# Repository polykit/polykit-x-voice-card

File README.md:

# Polykit-X Voice Card

This repository contains schematics and Kicad PCB layout for a voice card with pole-mixing multimode filter. Multiple cards like this are typically used in a polyphonic synthesizer. It can also be used in a monophonic setup. There is only minimal additional circuitry like some pots, input jacks and voltage regulators needed.

Voice card specs:

- Single oscillator with saw, triangle and pulse output
- Multiple VCAs to blend between different input signals, a main VCA for the envelope and a panning VCA for stereo output
- An additional external input that can be mixed in, eg. a noise signal
- One envelope generator for the VCA. It can modulate filter frequency and resonance, also with an inverted signal
- A pole-mixing multimode filter with 8 filter responses:
    - 4P LP
    - 2P LP
    - 4P HP
    - 2P HP
    - 4P BP
    - 2P BP
    - 3P AP + 1P LP
    - 4P N
- There are multiple options two switch and blend between different signals and filter responses
- PWM, FM and synchronization inputs

Video playlist on its functionality and design process: https://www.youtube.com/watch?v=2grRbG7IwDw&list=PLUKLEU8jmlbHH4_13YZM0MI6ez4gYQPfy

## Printed Circuit Boards

Geber files for PCB production [can be downloaded here](plots/).

## Pinout

| Pin # | Description          | Short         | Voltage Range | Type   | Direction | Note |
|-------|----------------------|---------------|---------------|--------|-----------|------|
| 1     | Ground               | GND           |               |        |           |
| 2     | +12V                 | +12V          |               |        |           |
| 3     | -12V                 | -12V          |               |        |           |
| 4     | +5V                  | +5V           |               |        |           |
| 5     | -5V                  | -5V           |               |        |           |
| 6     | Pitch control        | PITCH         | ±5V           | CV     |           | 1
| 7     | PWM                  | PWM           | 0V to 5V      | CV     |           |
| 8     | FM                   | FM            |               | Signal |           |
| 9     | Soft sync            | SSYNC         |               | Signal |           |
| 10    | Hard sync            | HSYNC         |               | Signal |           |
| 11    | Envelope Attack      | ADSR_A        | 0V to -5V     | CV     |           |
| 12    | Envelope Decay       | ADSR_D        | 0V to -5V     | CV     |           |
| 13    | Envelope Sustain     | ADSR_S        | 0V to 5V      | CV     |           |
| 14    | Envelope Release     | ADSR_R        | 0V to -5V     | CV     |           |
| 15    | Envelope Trigger     | TRIG          | 0V/5V         | Trig   |           |
| 16    | Envelope Gate        | GATE          | 0V/5V         | Gate   |           |
| 17    | Envelope Output      | ADSR_OUT      | 0V to 5V      | CV     |           |
| 18    | Enable saw signal    | SAW_ON        | 0V/5V         | Switch |           |
| 19    | Enable triangle sig. | TRIANGLE_ON   | 0V/5V         | Switch |           |
| 20    | Enable ext. signal   | EXTERNAL_ON   | 0V/5V         | Switch |           |
| 21    | Neg. freq. by ADSR   | FREQ_ADSR_NEQ | 0V/5V         | Switch |           |
| 22    | Freq. by ADSR        | FREQ_ADSR     | 0V/5V         | Switch |           |
| 23    | Res. by ADSR         | RES_ADSR      | 0V/5V         | Switch |           |
| 24    | Neg. res. by ADSR    | REF_ADSR_NEQ  | 0V/5V         | Switch |           |
| 25    | Input level 1        | LVL1          | 0V to 5V      | CV     |           |
| 26    | Input level 2        | LVL2          | 0V to 5V      | CV     |           |
| 27    | VCA                  | VCA_CV        | 0V to 5V      | CV     |           |
| 28    | Output panning       | PAN_CV        | -2V to 2V     | CV     |           |
| 29    | External input       | EXTERNAL_IN   |               | Signal |           |
| 30    | Freq. control        | FREQ_CV       | 0V to 5V      | CV     |           |
| 31    | Res. control         | RES_CV        | 0V to 5V      | CV     |           |
| 32    | Filter mode A        | FILTER_MODE_A | 0V/5V         | Switch |           |
| 33    | Filter mode B        | FILTER_MODE_B | 0V/5V         | Switch |           |
| 34    | Filter mode C        | FILTER_MODE_C | 0V/5V         | Switch |           |
| 35    | Output left          | OUT_L         |               | Signal |           | 2
| 36    | Output right         | OUT_R         |               | Signal |           | 2

Note 1: A 100k ohm resistor on pitch CV input is needed. Multiple CV sources can be added by using multiple resistors in parallel

Note 2: Max. output volume can be adjusted by changing R32/R33

## Filter modes

| # | C B A | Filter response |
|---|-------|-----------------|
| 0 | 0 0 0 | 4P LP           |
| 1 | 0 0 1 | 2P LP           |
| 2 | 0 1 0 | 4P HP           |
| 3 | 0 1 1 | 2P HP           |
| 4 | 1 0 0 | 4P BP           |
| 5 | 1 0 1 | 2P BP           |
| 6 | 1 1 0 | 3P AP + 1P LP   |
| 7 | 1 1 1 | 4P N            |

Select filter mode on pins 32-34

0=GND, 1=5V

## Tuning Procedure

### VCO

You need a control voltage 1V/octave source like a keyboard or two fixed, precise voltages in order to tune the VCO. Also a tuning device or a mobile tuning app is needed.

RV3 (TUNE) is for trimming the overall tune, RV5 (SCALE) is for adjusting the distance between two notes.

Take two notes that are one octave apart, eg. C3 and C4. play the first note and trim RV3 to that note.

Now go back and forth between both notes and adjust RV5 so that the correct distance between them gets closer. The first note will drift away while doing this so go back to it by adjusting RV3 again from time to time. Repeat this until both notes are perfectly in tune.

RV4 (HFT) is for trimming the higher frequencies if neccessary.

## BOM

|Reference                                                                                                      |Qnty|Value              |Description                                                                                           |
|---------------------------------------------------------------------------------------------------------|----|-------------------|------------------------------------------------------------------------------------------------------|
|C1, C2, C3, C4, C5, C6, C17, C18, C19, C20, C22, C27, C28, C33, C34, C35, C36, C37, C38, C39, C40       |21  |100n               |Unpolarized capacitor                                                                                 |
|C7, C9, C13, C14, C15, C16                                                                              |6   |2,2uF                |Polarized capacitor                                                                                   |
|C8,                                                                                                      |1   |330p               |Unpolarized capacitor, film or mylar                                                                              |
|C10, C11, C12                                                                                           |3   |33n                |Unpolarized capacitor, film or mylar                                                                                  |
|C21, C23                                                                                                |2   |1n                 |Unpolarized capacitor                                                                                 |
|C24, C25, C29, C30                                                                                      |4   |10n                |Unpolarized capacitor                                                                |
|C26                                                                                                     |1   |1n*                |Unpolarized capacitor, *polypropylene or similar                                                                                 |
|C31                                                                                                     |1   |10n*               |Unpolarized capacitor, *polypropylene or similar                                                                 |
|C32                                                                                                     |1   |33n*               |Unpolarized capacitor, *polypropylene or similar                                                                  |
|D1                                                                                                      |1   |1N4148             |100V 0.15A standard switching diode, DO-35                                                            |
|D2                                                                                                      |1   |LED                |3mm                                                                                  |
|J1                                                                                                      |1   |Conn_01x36         | Pin header 2.54mm 1x36pin 90 degree angle
|Q1                                                                                                      |1   |2N3904             | NPN Transistor, TO-92                                                  |
|R1, R3, R4, R43, R44                                                                                    |5   |1M                 |Resistor                                                                                              |
|R2, R28, R29, R38, R42                                                                                  |4   |470k               |Resistor                                                                                              |
|R5, R6, R7, R21, R22, R24, R25, R54, R55, R56, R60, R63, R68, R73, R74, R75, R76, R93, R101, R102, R103 |21  |10k                |Resistor                                                                                              |
|R8, R9, R10, R11, R12, R13, R14, R15, R18, R19, R20, R69, R70, R71                                      |14  |100k               |Resistor                                                                                              |
|R16, R17, R23                                                                                           |3   |20k                |Resistor                                                                                              |
|R26, R27, R41, R72                                                                                      |4   |68k                |Resistor                                                                                              |
|R30, R31, R34, R35, R37, R64, R65, R66, R67                                                             |9   |1k                 |Resistor                                                                                              |
|R32, R33, R36, R62                                                                                      |4   |33k                |Resistor                                                                                              |
|R39, R40                                                                                                |2   |22k                |Resistor                                                                                              |
|R45                                                                                                     |1   |330k               |Resistor                                                                                              |
|R46                                                                                                     |1   |1M5                |Resistor                                                                                              |
|R47, R48, R57, R58, R59                                                                                 |5   |470                |Resistor                                                                                              |
|R49                                                                                                     |1   |24k                |Resistor                                                                                              |
|R50                                                                                                     |1   |5k6                |Resistor                                                                                              |
|R51                                                                                                     |1   |1k8                |Resistor                                                                                              |
|R52                                                                                                     |1   |10M                |Resistor                                                                                              |
|R53                                                                                                     |1   |47k                |Resistor                                                                                              |
|R61                                                                                                     |1   |680                |Resistor                                                                                              |
|R77, R79, R80, R81, R82, R86, R87, R89, R90, R91, R92, R96                                              |12  |30k                |Resistor                                                                                              |
|R78, R88, R97, R98, R99, R100                                                                           |6   |15k                |Resistor                                                                                              |
|R83, R85, R95                                                                                           |3   |7k5                |Resistor                                                                                              |
|R84, R94                                                                                                |2   |4k99               |Resistor                                                                                              |
|R104                                                                                                    |1   |4k7                |Resistor                                                                                              |
|RV1                                                                                                     |1   |10k NEG_RES_OFFSET |Trim-potentiometer                                                                                    |
|RV2                                                                                                     |1   |10k NEG_FREQ_OFFSET|Trim-potentiometer                                                                                    |
|RV3                                                                                                     |1   |10k TUNE           |Trim-potentiometer                                                                                    |
|RV4                                                                                                     |1   |10k HFT            |Trim-potentiometer                                                                                    |
|RV5                                                                                                     |1   |10k SCALE          |Trim-potentiometer                                                                                    |
|U1, U3                                                                                                  |2   |4016               |Quad Analog Switches                                                                                  |
|U2                                                                                                      |1   |TL072              |Dual Low-Noise JFET-Input Operational Amplifiers, DIP-8/SOIC-8                                        |
|U4, U8, U9                                                                                              |3   |TL074              |Quad Low-Noise JFET-Input Operational Amplifiers, DIP-14/SOIC-14                                      |
|U5                                                                                                      |1   |AS3372E            |4-pole VCF, dual channel input mixer, VCA, panning VCA                                                                                                     |
|U6                                                                                                      |1   |AS3340             |Voltage Controlled Oscillator (VCO), DIP-16/SOIC-16                                                   |
|U7                                                                                                      |1   |AS3310             |ADSR Voltage Controlled Envelope Generator, DIP-16/SOIC-16                                            |
|U10                                                                                                     |1   |CD4051B            |CMOS single 8-channel analog multiplexer demultiplexer, TSSOP-16/DIP-16/SOIC-16                       |

## References

Article on Pole Mixing Filters: https://electricdruid.net/multimode-filters-part-2-pole-mixing-filters

Oberheim Matrix-12 Service Manual: https://archive.org/details/oberheim_MATRIX-12_SERVICE_MANUAL

Oberheim Xpander Service Manual: https://archive.org/details/oberheim_XPANDER_SERVICE_MANUAL

Sequential Prophet T8 Service Manual: https://archive.org/details/sm_SCI_T8_Service_Manual_Complete_sm

AS3372E Datasheet: https://www.ericasynths.lv/media/AS3372E.pdf

AS3310 Datasheet: https://www.alfarzpp.lv/eng/sc/AS3310.pdf

AS3340 Datasheet: https://www.alfarzpp.lv/eng/sc/AS3340.pdf

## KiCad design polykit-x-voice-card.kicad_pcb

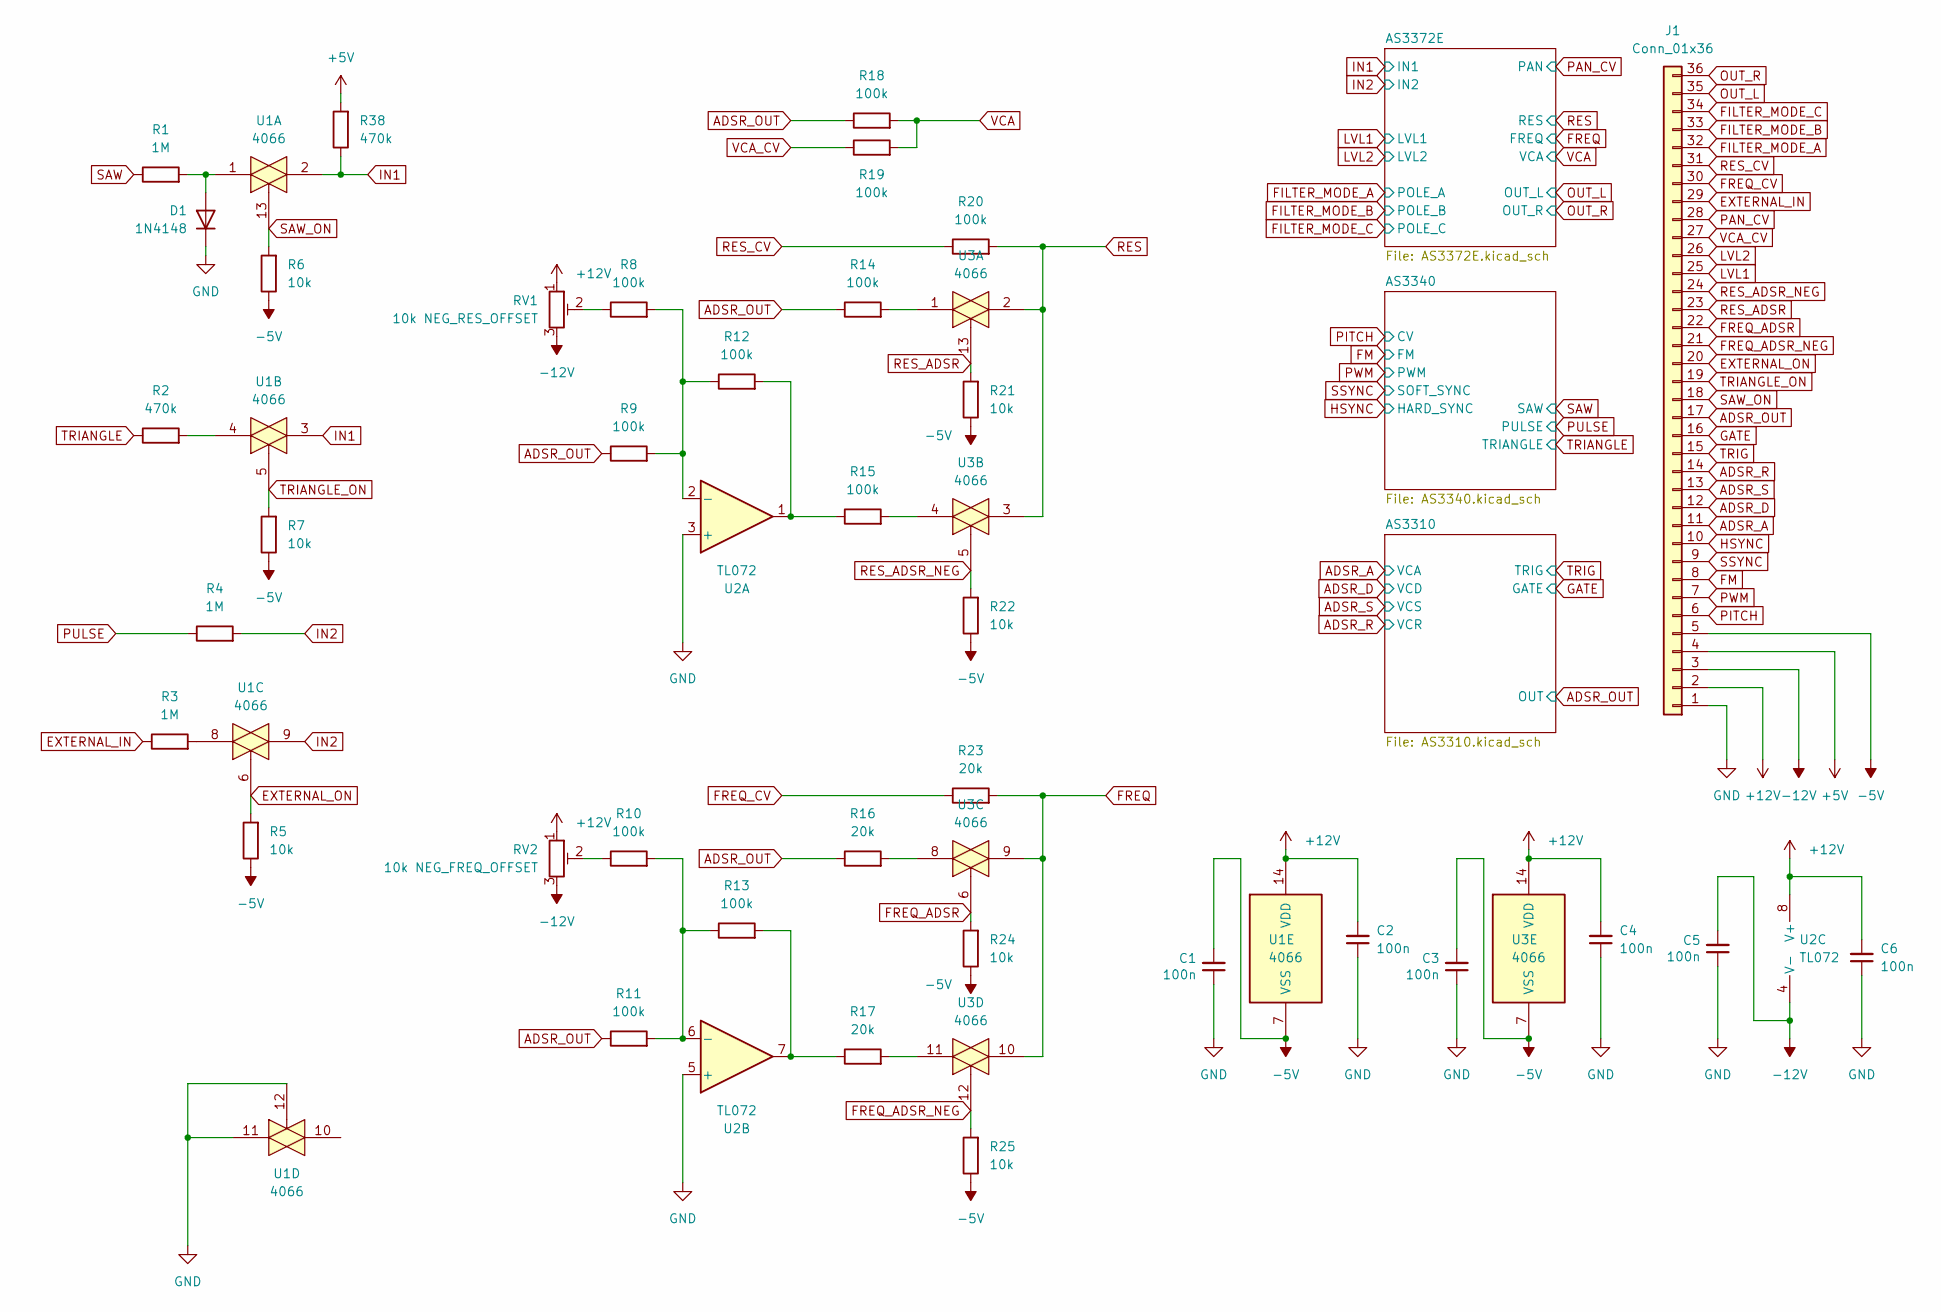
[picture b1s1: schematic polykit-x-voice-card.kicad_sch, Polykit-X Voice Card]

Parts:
C1, C2, C3, C4, C5, C6: 100n; C_Disc_D5.0mm_W2.5mm_P2.50mm
D1: 1N4148; D_DO-35_SOD27_P7.62mm_Horizontal
J1: Conn_01x36; PinHeader_1x36_P2.54mm_Horizontal
R1, R3, R4: 1M; R_Axial_DIN0207_L6.3mm_D2.5mm_P10.16mm_Horizontal
R2, R38: 470k; R_Axial_DIN0207_L6.3mm_D2.5mm_P10.16mm_Horizontal
R5, R6, R7, R21, R22, R24, R25: 10k; R_Axial_DIN0207_L6.3mm_D2.5mm_P10.16mm_Horizontal
R8, R9, R10, R11, R12, R13, R14, R15, R18, R19, R20: 100k; R_Axial_DIN0207_L6.3mm_D2.5mm_P10.16mm_Horizontal
R16, R17, R23: 20k; R_Axial_DIN0207_L6.3mm_D2.5mm_P10.16mm_Horizontal
RV1: 10k NEG_RES_OFFSET; Potentiometer_Bourns_3296W_Vertical
RV2: 10k NEG_FREQ_OFFSET; Potentiometer_Bourns_3296W_Vertical
U1, U3: 4066; DIP-14_W7.62mm_Socket_LongPads
U2: TL072; DIP-8_W7.62mm_Socket_LongPads

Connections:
+5V: J1.4, R38.2; also elsewhere on the board
+12V: C2.2, C4.2, C6.2, J1.2, RV1.1, RV2.1, U1.14 (VDD), U2.8 (V+), U3.14 (VDD); also elsewhere on the board
-5V: C1.2, C3.2, J1.5, R5.1, R6.1, R7.1, R21.1, R22.1, R24.1, R25.1, U1.7 (VSS), U3.7 (VSS); also elsewhere on the board
-12V: C5.2, J1.3, RV1.3, RV2.3, U2.4 (V-); also elsewhere on the board
ADSR_A: J1.11; also elsewhere on the board
ADSR_D: J1.12; also elsewhere on the board
ADSR_OUT: J1.17, R9.1, R11.1, R14.1, R16.1, R18.1; also elsewhere on the board
ADSR_R: J1.14; also elsewhere on the board
ADSR_S: J1.13; also elsewhere on the board
EXTERNAL_IN: J1.29, R3.1
EXTERNAL_ON: J1.20, R5.2, U1.6
FILTER_MODE_A: J1.32; also elsewhere on the board
FILTER_MODE_B: J1.33; also elsewhere on the board
FILTER_MODE_C: J1.34; also elsewhere on the board
FM: J1.8; also elsewhere on the board
FREQ: R23.2, U3.9, U3.10; also elsewhere on the board
FREQ_ADSR: J1.22, R24.2, U3.6
FREQ_ADSR_NEG: J1.21, R25.2, U3.12
FREQ_CV: J1.30, R23.1
GATE: J1.16; also elsewhere on the board
GND: C1.1, C2.1, C3.1, C4.1, C5.1, C6.1, D1.1 (K), J1.1, U1.11, U1.12, U2.3 (+), U2.5 (+); also elsewhere on the board
HSYNC: J1.10; also elsewhere on the board
IN1: R38.1, U1.2, U1.3; also elsewhere on the board
IN2: R4.2, U1.9; also elsewhere on the board
LVL1: J1.25; also elsewhere on the board
LVL2: J1.26; also elsewhere on the board
unnamed: D1.2 (A), R1.2, U1.1
unnamed: R2.2, U1.4
unnamed: R3.2, U1.8
unnamed: R8.1, RV1.2
unnamed: R10.1, RV2.2
unnamed: R10.2, R11.2, R13.1, U2.6 (-)
unnamed: R8.2, R9.2, R12.1, U2.2 (-)
unnamed: R12.2, R15.1, U2.1
unnamed: R13.2, R17.1, U2.7
unnamed: R14.2, U3.1
unnamed: R15.2, U3.4
unnamed: R16.2, U3.8
unnamed: R17.2, U3.11
OUT_L: J1.35; also elsewhere on the board
OUT_R: J1.36; also elsewhere on the board
PAN_CV: J1.28; also elsewhere on the board
PITCH: J1.6; also elsewhere on the board
PULSE: R4.1; also elsewhere on the board
PWM: J1.7; also elsewhere on the board
RES: R20.2, U3.2, U3.3; also elsewhere on the board
RES_ADSR: J1.23, R21.2, U3.13
RES_ADSR_NEG: J1.24, R22.2, U3.5
RES_CV: J1.31, R20.1
SAW: R1.1; also elsewhere on the board
SAW_ON: J1.18, R6.2, U1.13
SSYNC: J1.9; also elsewhere on the board
TRIANGLE: R2.1; also elsewhere on the board
TRIANGLE_ON: J1.19, R7.2, U1.5
TRIG: J1.15; also elsewhere on the board
VCA: R18.2, R19.2; also elsewhere on the board
VCA_CV: J1.27, R19.1

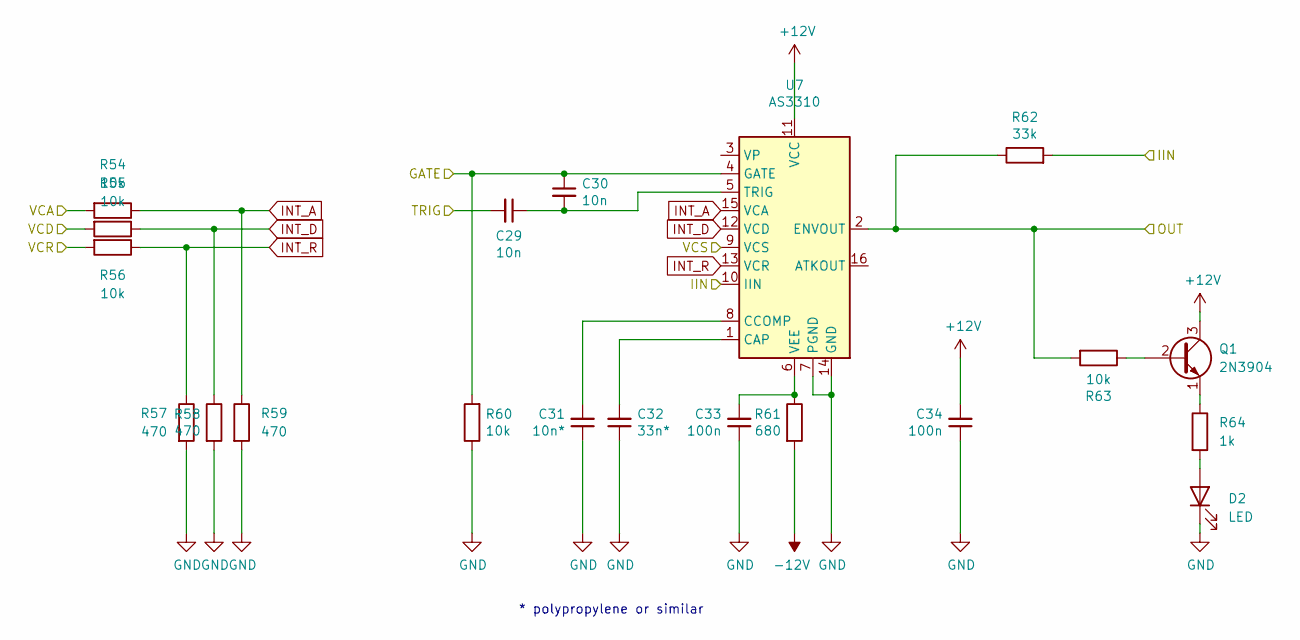
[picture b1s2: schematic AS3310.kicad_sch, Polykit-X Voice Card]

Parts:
C29, C30: 10n; C_Disc_D5.0mm_W2.5mm_P2.50mm
C31: 10n*; C_Rect_L7.2mm_W5.5mm_P5.00mm_FKS2_FKP2_MKS2_MKP2
C32: 33n*; C_Rect_L7.2mm_W5.5mm_P5.00mm_FKS2_FKP2_MKS2_MKP2
C33, C34: 100n; C_Disc_D5.0mm_W2.5mm_P2.50mm
D2: LED; LED_D3.0mm
Q1: 2N3904; TO-92_Inline_Wide
R54, R55, R56, R60, R63: 10k; R_Axial_DIN0207_L6.3mm_D2.5mm_P10.16mm_Horizontal
R57, R58, R59: 470; R_Axial_DIN0207_L6.3mm_D2.5mm_P10.16mm_Horizontal
R61: 680; R_Axial_DIN0207_L6.3mm_D2.5mm_P10.16mm_Horizontal
R62: 33k; R_Axial_DIN0207_L6.3mm_D2.5mm_P10.16mm_Horizontal
R64: 1k; R_Axial_DIN0207_L6.3mm_D2.5mm_P10.16mm_Horizontal
U7: AS3310; DIP-16_W7.62mm_Socket_LongPads

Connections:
+12V: C34.2, Q1.3 (C), U7.11 (VCC); also elsewhere on the board
-12V: R61.2; also elsewhere on the board
/AS3310/IIN: R62.2, U7.10 (IIN)
ADSR_A: R54.2; also elsewhere on the board
ADSR_D: R55.2; also elsewhere on the board
ADSR_OUT: R62.1, R63.2, U7.2 (ENVOUT); also elsewhere on the board
ADSR_R: R56.2; also elsewhere on the board
ADSR_S: U7.9 (VCS); also elsewhere on the board
GATE: C30.1, R60.2, U7.4 (GATE); also elsewhere on the board
GND: C31.1, C32.1, C33.1, C34.1, D2.1 (K), R57.2, R58.2, R59.2, R60.1, U7.7 (PGND), U7.14 (GND); also elsewhere on the board
INT_A: R54.1, R59.1, U7.15 (VCA)
INT_D: R55.1, R58.1, U7.12 (VCD)
INT_R: R56.1, R57.1, U7.13 (VCR)
unnamed: C29.1, C30.2, U7.5 (TRIG)
unnamed: C31.2, U7.8 (CCOMP)
unnamed: C32.2, U7.1 (CAP)
unnamed: C33.2, R61.1, U7.6 (VEE)
unnamed: D2.2 (A), R64.2
unnamed: Q1.1 (E), R64.1
unnamed: Q1.2 (B), R63.1
TRIG: C29.2; also elsewhere on the board

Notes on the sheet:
* polypropylene or similar

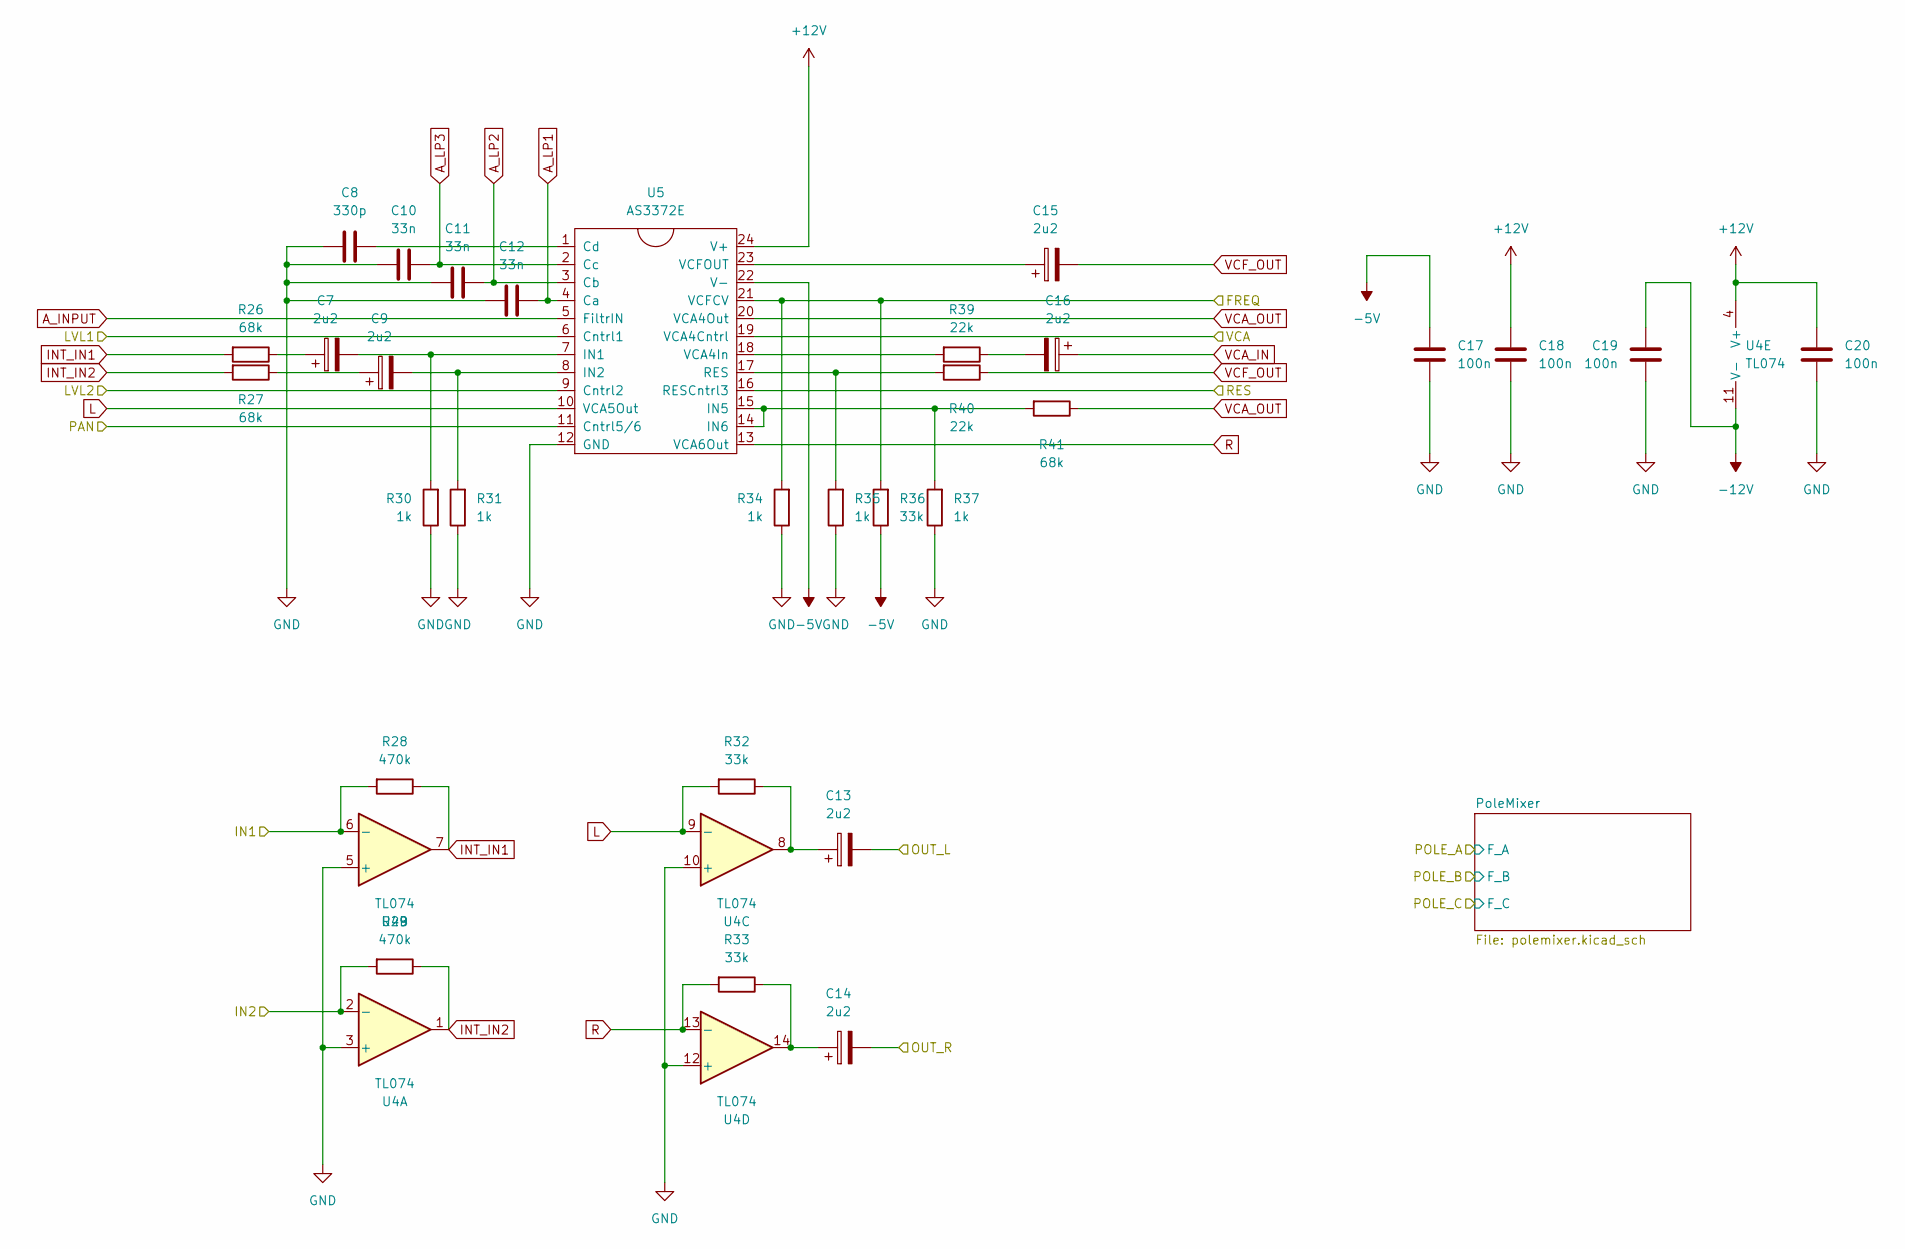
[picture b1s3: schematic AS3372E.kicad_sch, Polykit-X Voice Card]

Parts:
C7, C9, C13, C14, C15, C16: 2u2; CP_Radial_D5.0mm_P2.00mm
C8: 330p; C_Rect_L7.2mm_W3.0mm_P5.00mm_FKS2_FKP2_MKS2_MKP2
C10, C11, C12: 33n; C_Rect_L7.2mm_W3.0mm_P5.00mm_FKS2_FKP2_MKS2_MKP2
C17, C18, C19, C20: 100n; C_Disc_D5.0mm_W2.5mm_P2.50mm
R26, R27, R41: 68k; R_Axial_DIN0207_L6.3mm_D2.5mm_P10.16mm_Horizontal
R28, R29: 470k; R_Axial_DIN0207_L6.3mm_D2.5mm_P10.16mm_Horizontal
R30, R31, R34, R35, R37: 1k; R_Axial_DIN0207_L6.3mm_D2.5mm_P10.16mm_Horizontal
R32, R33, R36: 33k; R_Axial_DIN0207_L6.3mm_D2.5mm_P10.16mm_Horizontal
R39, R40: 22k; R_Axial_DIN0207_L6.3mm_D2.5mm_P10.16mm_Horizontal
U4: TL074; DIP-14_W7.62mm_Socket_LongPads
U5: AS3372E; DIP-24_W7.62mm_Socket_LongPads

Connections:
+12V: C18.1, C20.2, U4.4 (V+), U5.24 (V+); also elsewhere on the board
-5V: C17.1, R36.1, U5.22 (V-); also elsewhere on the board
-12V: C19.2, U4.11 (V-); also elsewhere on the board
A_INPUT: U5.5 (FiltrIN); also elsewhere on the board
A_LP1: C12.2, U5.4 (Ca); also elsewhere on the board
A_LP2: C11.2, U5.3 (Cb); also elsewhere on the board
A_LP3: C10.2, U5.2 (Cc); also elsewhere on the board
FREQ: R34.2, R36.2, U5.21 (VCFCV); also elsewhere on the board
GND: C8.1, C10.1, C11.1, C12.1, C17.2, C18.2, C19.1, C20.1, R30.1, R31.1, R34.1, R35.1, R37.1, U4.3 (+), U4.5 (+), U4.10 (+), U4.12 (+), U5.12 (GND); also elsewhere on the board
IN1: R28.2, U4.6 (-); also elsewhere on the board
IN2: R29.2, U4.2 (-); also elsewhere on the board
INT_IN1: R26.2, R28.1, U4.7
INT_IN2: R27.2, R29.1, U4.1
L: R32.2, U4.9 (-), U5.10 (VCA5Out)
LVL1: U5.6 (Cntrl1); also elsewhere on the board
LVL2: U5.9 (Cntrl2); also elsewhere on the board
unnamed: C7.1, R26.1
unnamed: C7.2, R30.2, U5.7 (IN1)
unnamed: C8.2, U5.1 (Cd)
unnamed: C9.1, R27.1
unnamed: C9.2, R31.2, U5.8 (IN2)
unnamed: C13.1, R32.1, U4.8
unnamed: C14.1, R33.1, U4.14
unnamed: C15.1, U5.23 (VCFOUT)
unnamed: C16.2, R39.1
unnamed: R35.2, R40.2, U5.17 (RES)
unnamed: R37.2, R41.2, U5.14 (IN6), U5.15 (IN5)
unnamed: R39.2, U5.18 (VCA4In)
OUT_L: C13.2; also elsewhere on the board
OUT_R: C14.2; also elsewhere on the board
PAN_CV: U5.11 (Cntrl5/6); also elsewhere on the board
R: R33.2, U4.13 (-), U5.13 (VCA6Out)
RES: U5.16 (RESCntrl3); also elsewhere on the board
VCA: U5.19 (VCA4Cntrl); also elsewhere on the board
VCA_IN: C16.1; also elsewhere on the board
VCA_OUT: R41.1, U5.20 (VCA4Out)
VCF_OUT: C15.2, R40.1; also elsewhere on the board

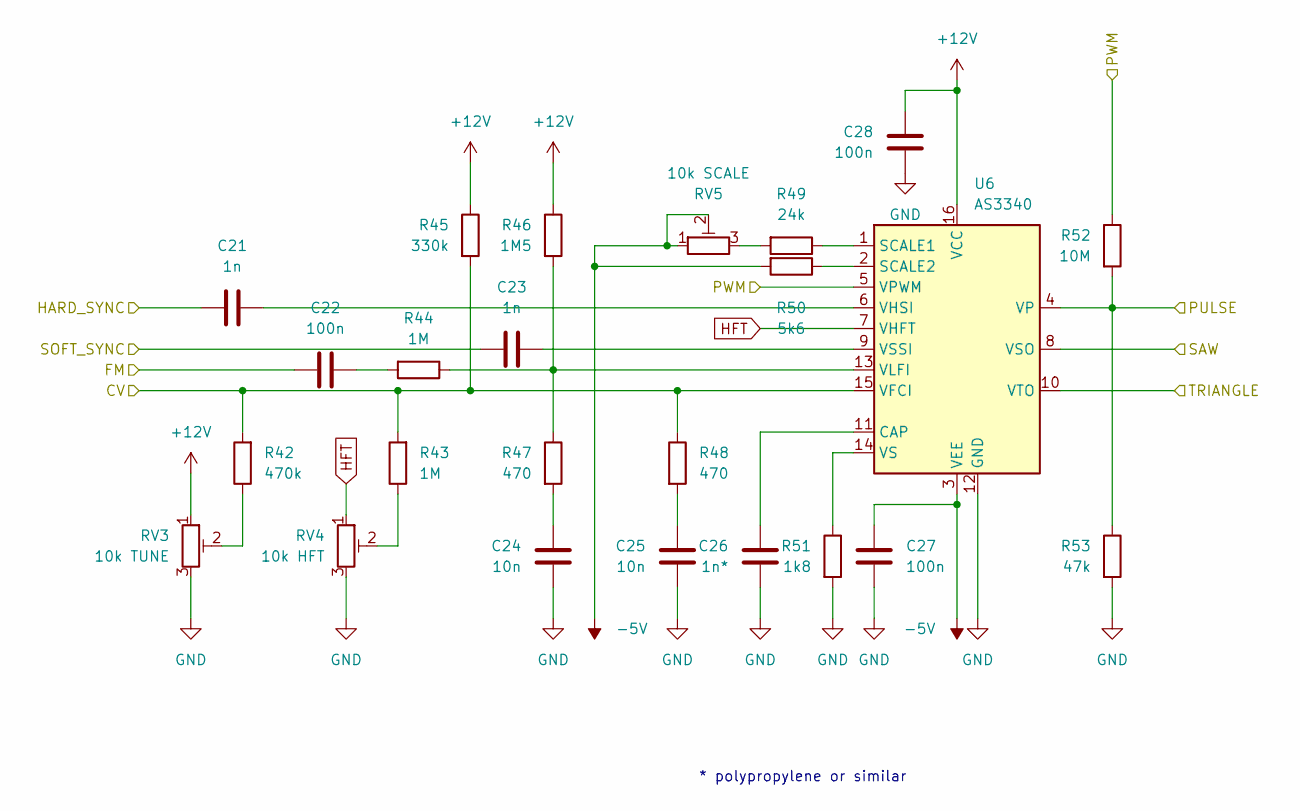
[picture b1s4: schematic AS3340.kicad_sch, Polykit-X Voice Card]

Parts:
C21, C23: 1n; C_Disc_D5.0mm_W2.5mm_P2.50mm
C22, C27, C28: 100n; C_Disc_D5.0mm_W2.5mm_P2.50mm
C24, C25: 10n; C_Disc_D5.0mm_W2.5mm_P2.50mm
C26: 1n*; C_Rect_L7.2mm_W4.5mm_P5.00mm_FKS2_FKP2_MKS2_MKP2
R42: 470k; R_Axial_DIN0207_L6.3mm_D2.5mm_P10.16mm_Horizontal
R43, R44: 1M; R_Axial_DIN0207_L6.3mm_D2.5mm_P10.16mm_Horizontal
R45: 330k; R_Axial_DIN0207_L6.3mm_D2.5mm_P10.16mm_Horizontal
R46: 1M5; R_Axial_DIN0207_L6.3mm_D2.5mm_P10.16mm_Horizontal
R47, R48: 470; R_Axial_DIN0207_L6.3mm_D2.5mm_P10.16mm_Horizontal
R49: 24k; R_Axial_DIN0207_L6.3mm_D2.5mm_P10.16mm_Horizontal
R50: 5k6; R_Axial_DIN0207_L6.3mm_D2.5mm_P10.16mm_Horizontal
R51: 1k8; R_Axial_DIN0207_L6.3mm_D2.5mm_P10.16mm_Horizontal
R52: 10M; R_Axial_DIN0207_L6.3mm_D2.5mm_P10.16mm_Horizontal
R53: 47k; R_Axial_DIN0207_L6.3mm_D2.5mm_P10.16mm_Horizontal
RV3: 10k TUNE; Potentiometer_Bourns_3296W_Vertical
RV4: 10k HFT; Potentiometer_Bourns_3296W_Vertical
RV5: 10k SCALE; Potentiometer_Bourns_3296W_Vertical
U6: AS3340; DIP-16_W7.62mm_Socket_LongPads

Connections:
+12V: C28.1, R45.1, R46.1, RV3.1, U6.16 (VCC); also elsewhere on the board
-5V: C27.1, R50.2, RV5.1, RV5.2, U6.3 (VEE); also elsewhere on the board
FM: C22.2; also elsewhere on the board
GND: C24.2, C25.2, C26.2, C27.2, C28.2, R51.2, R53.2, RV3.3, RV4.3, U6.12 (GND); also elsewhere on the board
HFT: RV4.1, U6.7 (VHFT)
HSYNC: C21.1; also elsewhere on the board
unnamed: C21.2, U6.6 (VHSI)
unnamed: C22.1, R44.2
unnamed: C23.2, U6.9 (VSSI)
unnamed: C24.1, R47.2
unnamed: C25.1, R48.2
unnamed: C26.1, U6.11 (CAP)
unnamed: R42.1, RV3.2
unnamed: R43.1, RV4.2
unnamed: R44.1, R46.2, R47.1, U6.13 (VLFI)
unnamed: R49.1, U6.1 (SCALE1)
unnamed: R49.2, RV5.3
unnamed: R50.1, U6.2 (SCALE2)
unnamed: R51.1, U6.14 (VS)
PITCH: R42.2, R43.2, R45.2, R48.1, U6.15 (VFCI); also elsewhere on the board
PULSE: R52.2, R53.1, U6.4 (VP); also elsewhere on the board
PWM: R52.1, U6.5 (VPWM); also elsewhere on the board
SAW: U6.8 (VSO); also elsewhere on the board
SSYNC: C23.1; also elsewhere on the board
TRIANGLE: U6.10 (VTO); also elsewhere on the board

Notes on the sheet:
* polypropylene or similar

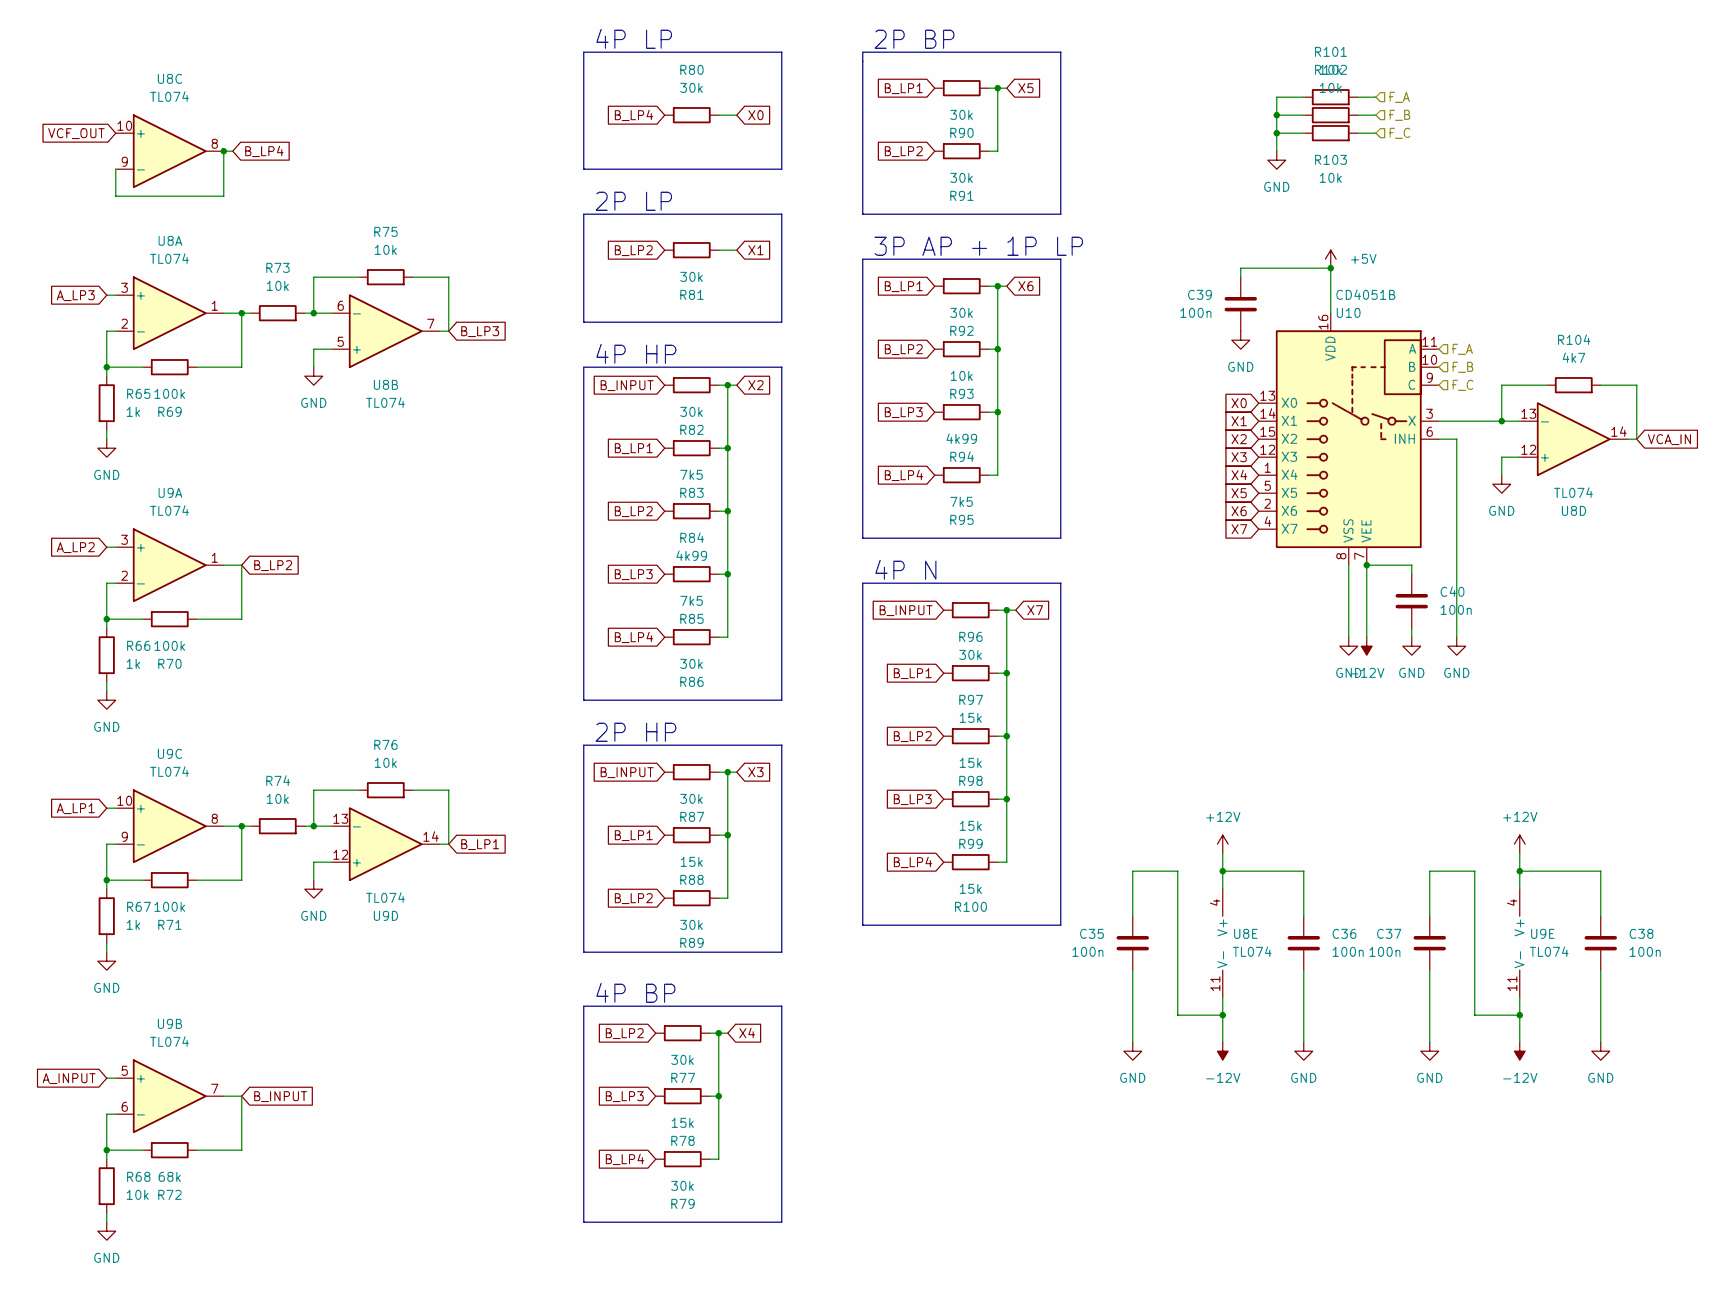
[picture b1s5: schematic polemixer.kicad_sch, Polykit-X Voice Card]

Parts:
C35, C36, C37, C38, C39, C40: 100n; C_Disc_D5.0mm_W2.5mm_P2.50mm
R65, R66, R67: 1k; R_Axial_DIN0207_L6.3mm_D2.5mm_P10.16mm_Horizontal
R68, R73, R74, R75, R76, R93, R101, R102, R103: 10k; R_Axial_DIN0207_L6.3mm_D2.5mm_P10.16mm_Horizontal
R69, R70, R71: 100k; R_Axial_DIN0207_L6.3mm_D2.5mm_P10.16mm_Horizontal
R72: 68k; R_Axial_DIN0207_L6.3mm_D2.5mm_P10.16mm_Horizontal
R77, R79, R80, R81, R82, R86, R87, R89, R90, R91, R92, R96: 30k; R_Axial_DIN0207_L6.3mm_D2.5mm_P10.16mm_Horizontal
R78, R88, R97, R98, R99, R100: 15k; R_Axial_DIN0207_L6.3mm_D2.5mm_P10.16mm_Horizontal
R83, R85, R95: 7k5; R_Axial_DIN0207_L6.3mm_D2.5mm_P10.16mm_Horizontal
R84, R94: 4k99; R_Axial_DIN0207_L6.3mm_D2.5mm_P10.16mm_Horizontal
R104: 4k7; R_Axial_DIN0207_L6.3mm_D2.5mm_P10.16mm_Horizontal
U8, U9: TL074; DIP-14_W7.62mm_Socket_LongPads
U10: CD4051B; DIP-16_W7.62mm_Socket_LongPads

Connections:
+5V: C39.2, U10.16 (VDD); also elsewhere on the board
+12V: C36.2, C38.2, U8.4 (V+), U9.4 (V+); also elsewhere on the board
-12V: C35.2, C37.2, C40.2, U8.11 (V-), U9.11 (V-), U10.7 (VEE); also elsewhere on the board
A_INPUT: U9.5 (+); also elsewhere on the board
A_LP1: U9.10 (+); also elsewhere on the board
A_LP2: U9.3 (+); also elsewhere on the board
A_LP3: U8.3 (+); also elsewhere on the board
B_INPUT: R72.1, R82.2, R87.2, R96.2, U9.7
B_LP1: R76.2, R83.2, R88.2, R90.2, R92.2, R97.2, U9.14
B_LP2: R70.1, R77.2, R81.2, R84.2, R89.2, R91.2, R93.2, R98.2, U9.1
B_LP3: R75.2, R78.2, R85.2, R94.2, R99.2, U8.7
B_LP4: R79.2, R80.2, R86.2, R95.2, R100.2, U8.8, U8.9 (-)
FILTER_MODE_A: R101.2, U10.11 (A); also elsewhere on the board
FILTER_MODE_B: R102.2, U10.10 (B); also elsewhere on the board
FILTER_MODE_C: R103.2, U10.9 (C); also elsewhere on the board
GND: C35.1, C36.1, C37.1, C38.1, C39.1, C40.1, R65.2, R66.2, R67.2, R68.2, R101.1, R102.1, R103.1, U8.5 (+), U8.12 (+), U9.12 (+), U10.6 (INH), U10.8 (VSS); also elsewhere on the board
unnamed: R65.1, R69.2, U8.2 (-)
unnamed: R66.1, R70.2, U9.2 (-)
unnamed: R67.1, R71.2, U9.9 (-)
unnamed: R68.1, R72.2, U9.6 (-)
unnamed: R69.1, R73.1, U8.1
unnamed: R71.1, R74.1, U9.8
unnamed: R73.2, R75.1, U8.6 (-)
unnamed: R74.2, R76.1, U9.13 (-)
unnamed: R104.1, U8.13 (-), U10.3 (X)
VCA_IN: R104.2, U8.14; also elsewhere on the board
VCF_OUT: U8.10 (+); also elsewhere on the board
X0: R80.1, U10.13 (X0)
X1: R81.1, U10.14 (X1)
X2: R82.1, R83.1, R84.1, R85.1, R86.1, U10.15 (X2)
X3: R87.1, R88.1, R89.1, U10.12 (X3)
X4: R77.1, R78.1, R79.1, U10.1 (X4)
X5: R90.1, R91.1, U10.5 (X5)
X6: R92.1, R93.1, R94.1, R95.1, U10.2 (X6)
X7: R96.1, R97.1, R98.1, R99.1, R100.1, U10.4 (X7)

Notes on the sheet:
2P LP
2P HP
3P AP + 1P LP
4P LP
4P BP
2P BP
4P HP
4P N

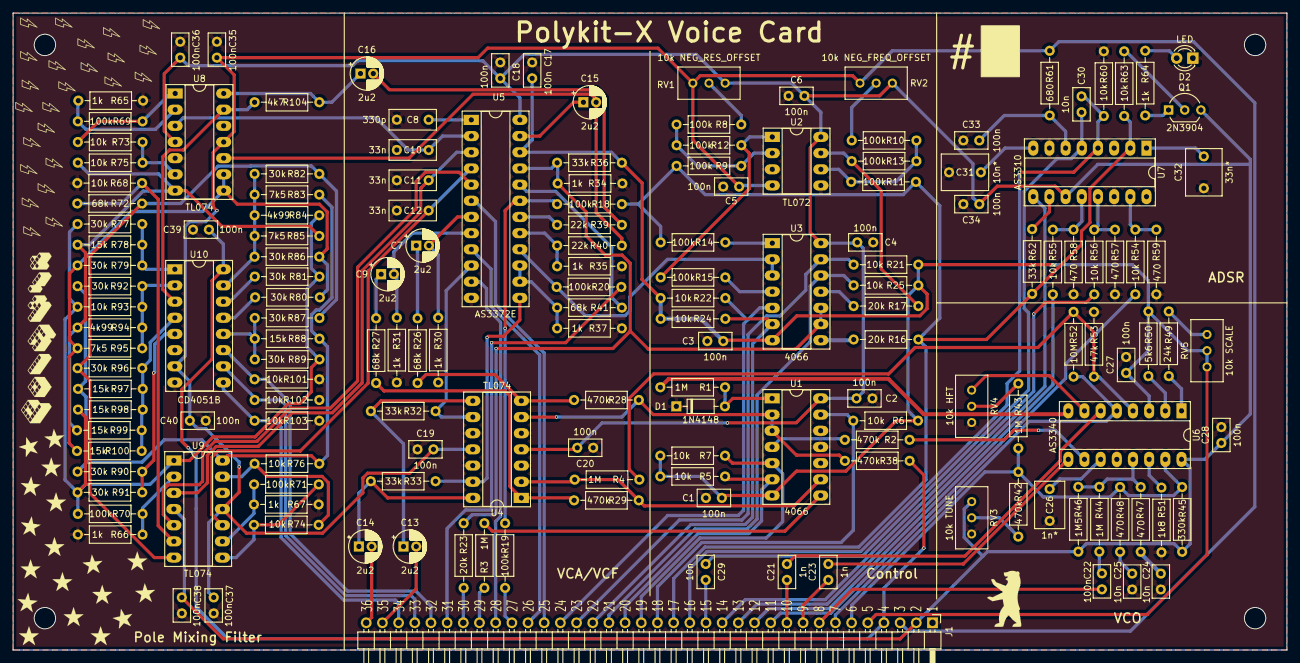
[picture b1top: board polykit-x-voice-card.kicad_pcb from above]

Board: 2 copper layers, 200.0 x 100.0 mm, 163 parts (0 on the bottom side), 127 nets.

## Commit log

2022-06-19 Initial import
2022-08-23 - add R38 offset to IN1 - change 4016 to 4066
2022-12-17 Fix bom
2023-01-26 Bump to v1.0.0
2023-02-06 Update pdf schematics
2023-09-15 Add vco tuning to readme
2023-12-24 Fix readme
2025-05-09 Add license
